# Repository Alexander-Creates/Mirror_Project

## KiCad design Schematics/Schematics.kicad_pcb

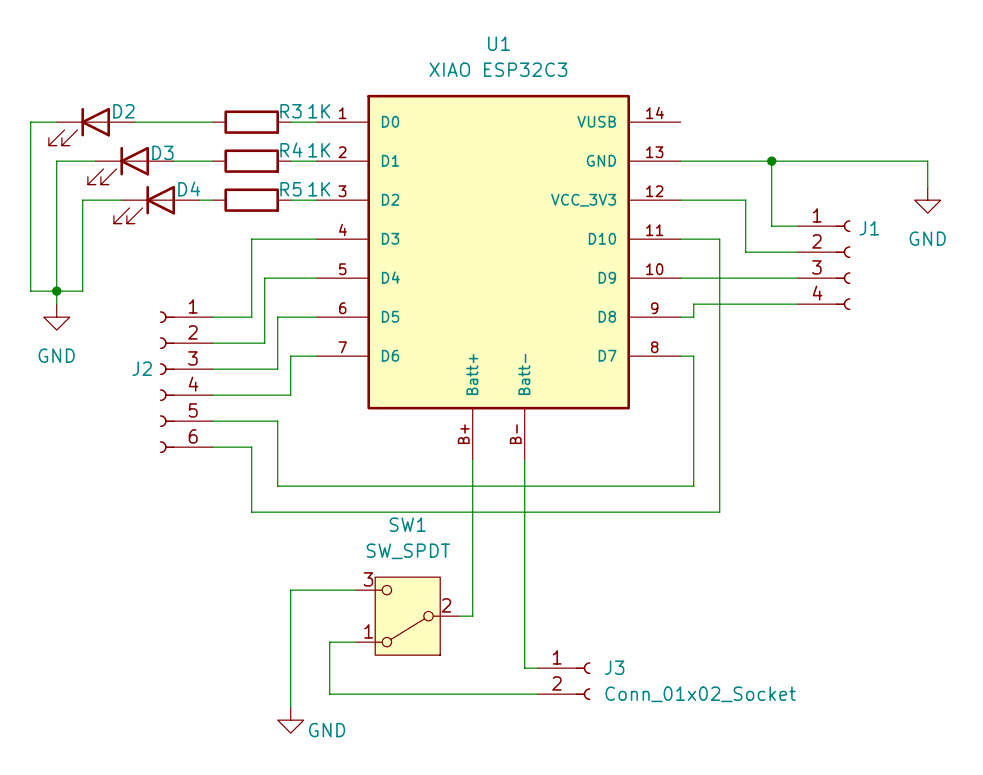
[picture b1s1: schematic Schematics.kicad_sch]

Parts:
D2, D3, D4: LED; LED_0603_1608Metric
J1: Conn_01x04_Socket; PinSocket_1x04_P2.54mm_Vertical
J2: Conn_01x06_Socket; PinSocket_1x06_P2.54mm_Vertical
J3: Conn_01x02_Socket; PinSocket_1x02_P2.54mm_Vertical
R3, R4, R5: 1K; R_0603_1608Metric
SW1: SW_SPDT; SW_SPDT_PCM12
U1: XIAO ESP32C3; xiao_esp32c3

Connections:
GND: D2.1 (K), D3.1 (K), D4.1 (K), J1.1, SW1.3 (C), U1.13 (GND)
unnamed: D2.2 (A), R3.1
unnamed: D3.2 (A), R4.1
unnamed: D4.2 (A), R5.1
unnamed: J1.2, U1.12 (VCC_3V3)
unnamed: J1.3, U1.10 (D9)
unnamed: J1.4, U1.9 (D8)
unnamed: J2.1, U1.4 (D3)
unnamed: J2.2, U1.5 (D4)
unnamed: J2.3, U1.6 (D5)
unnamed: J2.4, U1.7 (D6)
unnamed: J2.5, U1.8 (D7)
unnamed: J2.6, U1.11 (D10)
unnamed: J3.1, U1.B- (Batt-)
unnamed: J3.2, SW1.1 (A)
unnamed: SW1.2 (B), U1.B+ (Batt+)
unnamed: R3.2, U1.1 (D0)
unnamed: R4.2, U1.2 (D1)
unnamed: R5.2, U1.3 (D2)

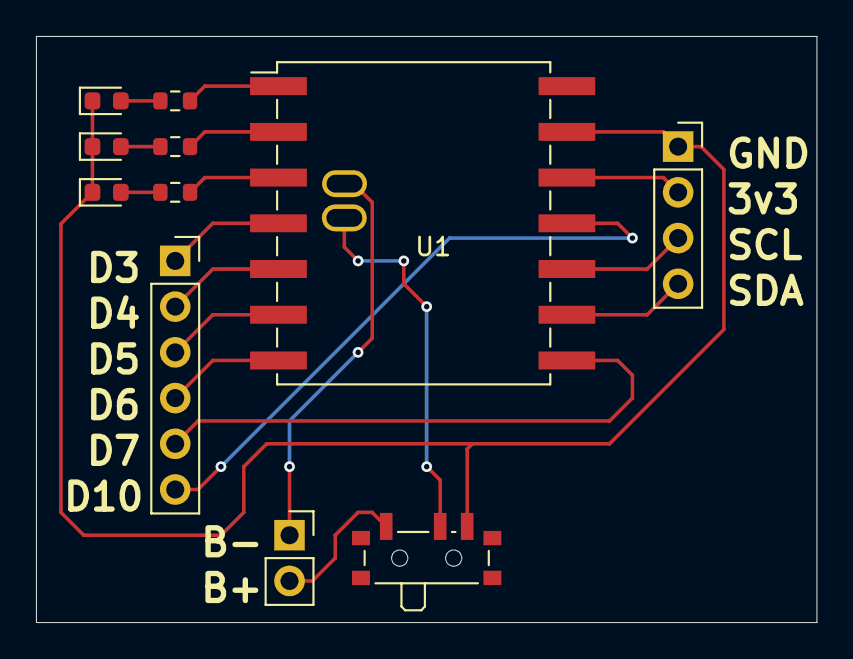
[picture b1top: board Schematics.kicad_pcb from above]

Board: 2 copper layers, 43.4 x 32.6 mm, 11 parts (0 on the bottom side), 19 nets.

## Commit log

2025-08-30 created branch
2025-10-06 Added Decoding SW (Python)
2025-10-06 Added c version, need to test as this may not work)
2026-03-06 added base connection from raw HEX to EUC world via PC and Arduino FW.
2026-03-06 updated arduino code to include LED indicators.
2026-03-06 updated arduino code - updated LED indicators
2026-03-29 added schematic for EUC mirror
2026-03-29 removed external charge module as it is already included
2026-03-29 redesign of the display and LEDs
2026-04-21 added GC9A01A lcd and LVGL functionality
2026-04-21 Added linear interpolation to arc values
2026-04-24 Began updating to reflect real world status
2026-04-25 Added battery voltage monitoring
2026-04-25 added 3d model and project
